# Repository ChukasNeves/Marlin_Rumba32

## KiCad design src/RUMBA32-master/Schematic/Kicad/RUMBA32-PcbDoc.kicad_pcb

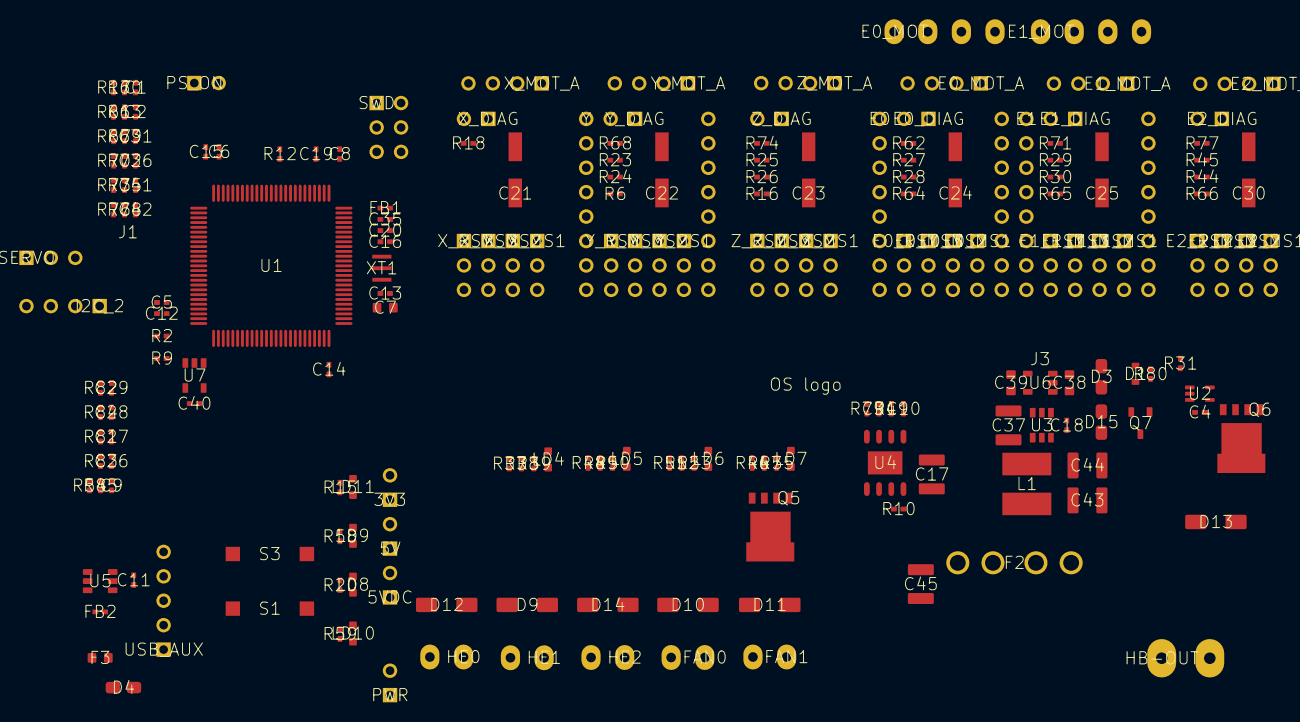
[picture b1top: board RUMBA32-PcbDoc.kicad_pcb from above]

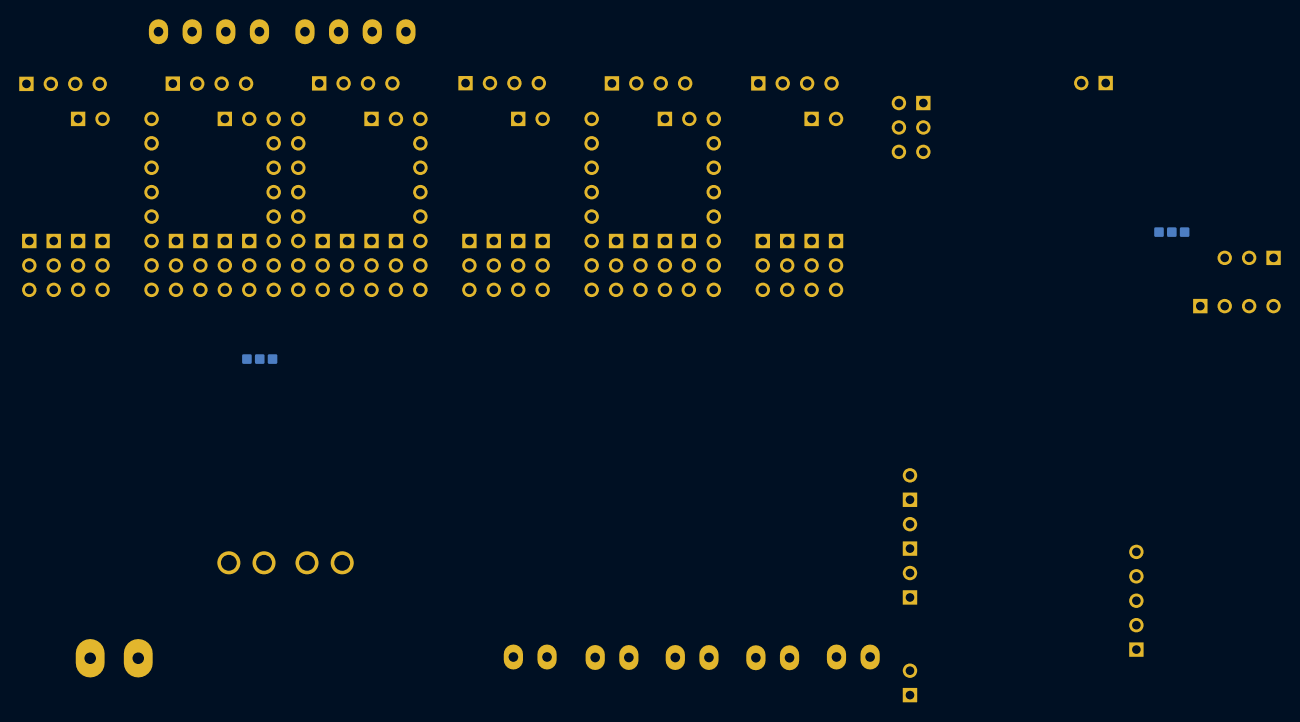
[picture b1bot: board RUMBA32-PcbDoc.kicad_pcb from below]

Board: 4 copper layers, 200 parts (3 on the bottom side), 140 nets, no tracks yet.

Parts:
3V3: 3V3; HDR1X2-HEADER
5V: 5V; HDR1X2-HEADER
5VDC: 5VDC; HDR1X2-HEADER
C1: C1; CAPC1005X55N
C2: C2; CAPC1005X55N
C4: C4; CAP 1005-0402
C5: C5; CAP 1005-0402
C6: C6; CAP 1005-0402
C7: C7; CAPC1608X90N
C8: C8; CAP 1005-0402
C9: C9; CAPC1005X55N
C10: C10; CAP 1005-0402
C11: C11; CAP 1005-0402
C12: C12; CAPC1005X55N
C13: C13; CAP 1005-0402
C14: C14; CAP 1005-0402
C15: C15; CAP 1005-0402
C16: C16; CAP 1005-0402
C17: C17; CAPC3225X220N
C18: C18; CAP 1005-0402
C19: C19; CAP 1005-0402
C20: C20; CAP 1005-0402
C21: C21; CAP EL PANASONIC
C22: C22; CAP EL PANASONIC
C23: C23; CAP EL PANASONIC
C24: C24; CAP EL PANASONIC
C25: C25; CAP EL PANASONIC
C26: C26; CAPC1005X55N
C27: C27; CAPC1005X55N
C28: C28; CAPC1005X55N
C29: C29; CAPC1005X55N
C30: C30; CAP EL PANASONIC
C31: C31; CAPC1005X55N
C34: C34; CAP 1005-0402
C35: C35; CAP 1005-0402
C36: C36; CAPC1005X55N
C37: C37; CAPC3225X220N
C38: C38; CAPC1608X90N
C39: C39; CAPC1608X90N
C40: C40; CAP 1005-0402
C41: C41; CAPC1005X55N
C42: C42; CAPC1005X55N
C43: C43; CAPC3225X220N
C44: C44; CAPC3225X220N
C45: C45; CAPC3225X220N
D1: D1; SOD523
D3: D3; DIOM2616X08N
D4: D4; DIOM2616X08N
D9: D9; DO-214AC
D10: D10; DO-214AC
D11: D11; DO-214AC
D12: D12; DO-214AC
D13: D13; DO-214AC
D14: D14; DO-214AC
D15: D15; DIOM2616X08N
E0: E0; A4988BREAKOUT_2
E0_DIAG: E0_DIAG; HDR1X2-HEADER Female
E0_MOT: E0_MOT; TERM4 3.5MM
E0_MOT_A: E0_MOT_A; HDR1X4
E0_MS1: E0_MS1; HDR1X3-HEADER
E0_MS2: E0_MS2; HDR1X3-HEADER
E0_MS3: E0_MS3; HDR1X3-HEADER
E0_RST: E0_RST; HDR1X3-HEADER
E1: E1; A4988BREAKOUT_2
E1_DIAG: E1_DIAG; HDR1X2-HEADER Female
E1_MOT: E1_MOT; TERM4 3.5MM
E1_MOT_A: E1_MOT_A; HDR1X4
E1_MS1: E1_MS1; HDR1X3-HEADER
E1_MS2: E1_MS2; HDR1X3-HEADER
E1_MS3: E1_MS3; HDR1X3-HEADER
E1_RST: E1_RST; HDR1X3-HEADER
E2_DIAG: E2_DIAG; HDR1X2-HEADER Female
E2_MOT_A: E2_MOT_A; HDR1X4
E2_MS1: E2_MS1; HDR1X3-HEADER
E2_MS2: E2_MS2; HDR1X3-HEADER
E2_MS3: E2_MS3; HDR1X3-HEADER
E2_RST: E2_RST; HDR1X3-HEADER
F2: F2; FUSEHOLDER - BK-6013 - MINI ATC ATO BLADE 15A
F3: F3; FUSE 1608-0603
FAN0: FAN0; TERM2 3.5MM
FAN1: FAN1; TERM2 3.5MM
FB1: FB1; RESC1005X40N
FB2: FB2; RESC1005X40N
HB-OUT: HB-OUT; TERM2 5MM
HE0: HE0; TERM2 3.5MM
HE1: HE1; TERM2 3.5MM
HE2: HE2; TERM2 3.5MM
I2C_2: I2C_2; HDR1X4-HEADER
J1: J1; Jump_3Way - SMALL
J3: J3; Jump_3Way - SMALL
L1: L1; SRN6045TA SMD Inductor
LD4: LD4; LED 1608-0603
LD5: LD5; LED 1608-0603
LD6: LD6; LED 1608-0603
LD7: LD7; LED 1608-0603
LD8: LD8; LED 1608-0603
LD9: LD9; LED 1608-0603
LD10: LD10; LED 1608-0603
LD11: LD11; LED 1608-0603
OS logo: OS logo; OS LOGO TOP
PS_ON: PS_ON; HDR1X2-HEADER
PWR: PWR; HDR1X2-HEADER
Q5: Q5; LFPACK
Q6: Q6; LFPACK
Q7: Q7; SOT23-3 New
R2: R2; RESC1005X40N
R6: R6; RESC1005X40N
R9: R9; RESC1005X40N
R10: R10; RESC1005X40N
R12: R12; RESC1005X40N
R15: R15; RESC1005X40N
R16: R16; RESC1005X40N
R17: R17; RESC1005X40N
R18: R18; RESC1005X40N
R19: R19; RESC1005X40N
R20: R20; RESC1005X40N
R23: R23; RESC1005X40N
R24: R24; RESC1005X40N
R25: R25; RESC1005X40N
R26: R26; RESC1005X40N
R27: R27; RESC1005X40N
R28: R28; RESC1005X40N
R29: R29; RESC1005X40N
R30: R30; RESC1005X40N
R31: R31; RESC1005X40N
R37: R37; RESC1005X40N
R38: R38; RESC1005X40N
R39: R39; RESC1005X40N
R44: R44; RESC1005X40N
R45: R45; RESC1005X40N
R46: R46; RESC1005X40N
R47: R47; RESC1005X40N
R48: R48; RESC1005X40N
R49: R49; RESC1005X40N
R50: R50; RESC1005X40N
R51: R51; RESC1005X40N
R52: R52; RESC1005X40N
R53: R53; RESC1005X40N
R54: R54; RESC1005X40N
R55: R55; RESC1005X40N
R58: R58; RESC1005X40N
R59: R59; RESC1005X40N
R60: R60; RESC1005X40N
R61: R61; RESC1005X40N
R62: R62; RESC1005X40N
R63: R63; RESC1005X40N
R64: R64; RESC1005X40N
R65: R65; RESC1005X40N
R66: R66; RESC1005X40N
R67: R67; RESC1005X40N
R68: R68; RESC1005X40N
R69: R69; RESC1005X40N
R70: R70; RESC1005X40N
R71: R71; RESC1005X40N
R72: R72; RESC1005X40N
R73: R73; RESC1005X40N
R74: R74; RESC1005X40N
R75: R75; RESC1005X40N
R76: R76; RESC1005X40N
R77: R77; RESC1005X40N
R78: R78; RESC1005X40N
R79: R79; RESC1005X40N
R80: R80; RESC1005X40N
R81: R81; RESC1005X40N
R82: R82; RESC1005X40N
R83: R83; RESC1005X40N
R84: R84; RESC1005X40N
R85: R85; RESC1005X40N
S1: S1; SW-PB SMD 2pin
S3: S3; SW-PB SMD 2pin
SERVO: SERVO; HDR1X3-HEADER
SWD: SWD; HDR2X3
U1: U1; STM-LQFP100_N
U2: U2; SOT353
U3: U3; TSOT23-6
U4: U4; SOIC127P600X170_HS-9N
U5: U5; TSOT23-6
U6: U6; SOT23-5
U7: U7; SOT23-5
USB_AUX: USB_AUX; HDR1X5-HEADER
XT1: XT1; CERALOCK CSTCE_G
X_DIAG: X_DIAG; HDR1X2-HEADER Female
X_MOT_A: X_MOT_A; HDR1X4
X_MS1: X_MS1; HDR1X3-HEADER
X_MS2: X_MS2; HDR1X3-HEADER
X_MS3: X_MS3; HDR1X3-HEADER
X_RST: X_RST; HDR1X3-HEADER
Y: Y; A4988BREAKOUT_2
Y_DIAG: Y_DIAG; HDR1X2-HEADER Female
Y_MOT_A: Y_MOT_A; HDR1X4
Y_MS1: Y_MS1; HDR1X3-HEADER
Y_MS2: Y_MS2; HDR1X3-HEADER
Y_MS3: Y_MS3; HDR1X3-HEADER
Y_RST: Y_RST; HDR1X3-HEADER
Z_DIAG: Z_DIAG; HDR1X2-HEADER Female
Z_MOT_A: Z_MOT_A; HDR1X4
Z_MS1: Z_MS1; HDR1X3-HEADER
Z_MS2: Z_MS2; HDR1X3-HEADER
Z_MS3: Z_MS3; HDR1X3-HEADER
Z_RST: Z_RST; HDR1X3-HEADER

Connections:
5V_DCDC: 5VDC.1, C43.2, C44.2, D15.A, L1.2, LD8.1, R79.2, U3.1
+3V3: 3V3.1, C7.2, C12.2, C13.2, C14.2, C15.2, C16.2, C19.2, C39.2, C40.2, FB1.2, J1.1, J3.1, LD11.1, R2.2, S3.1, SWD.2, U1.6, U1.11, U1.19, U1.28, U1.50, U1.75, U1.100, U6.5, U7.4
+3V3A: C20.2, C35.2, FB1.1, R54.1, U1.21, U1.22
+5V: 5V.1, C4.2, C38.2, D3.A, D4.K, D15.K, I2C_2.4, J1.3, J3.3, LD9.1, R80.2, SERVO.2, U2.5, U6.1, U6.3
+12V: C45.2, LD10.1
+DRV: E0.10, E0_MS1.1, E0_MS2.1, E0_MS3.1, E1.10, E1_MS1.1, E1_MS2.1, E1_MS3.1, E2_MS1.1, E2_MS2.1, E2_MS3.1, J3.2, R23.1, R25.1, R27.1, R29.1, R45.1, X_MS1.1, X_MS2.1, X_MS3.1, Y.10, Y_MS1.1, Y_MS2.1, Y_MS3.1, Z_MS1.1, Z_MS2.1, Z_MS3.1
+V_STOP: J1.2, R17.1, R61.1, R67.1, R70.1, R73.1, R76.1
BOOT0: S3.2, SWD.4, U1.94
BTN_EN2: R12.2, U1.37
E0-CS/RX: E0_MS3.3, R64.1, U1.7
E0-DIR: E0.8, U1.92
E0-EN: E0.1, R27.2, U1.80
E0-SLP: E0.6, E0_RST.1
E0-STEP: E0.7, U1.91
E0-TX: R64.2, U1.58
E1-CS/RX: E1_MS3.3, R65.1, U1.86
E1-DIR: E1.8, U1.88
E1-EN: E1.1, R29.2, U1.85
E1-SLP: E1.6, E1_RST.1
E1-STEP: E1.7, U1.87
E1-TX: R65.2, U1.89
E2-CS/RX: E2_MS3.3, R66.1, U1.82
E2-EN: R45.2, U1.81
E2-TX: R66.2, U1.90
FAN_0: R46.1, R47.1, R55.2, U1.67
FAN_1: R51.1, R52.1, R53.2, U1.66
GND: 3V3.2, 5V.2, 5VDC.2, C1.1, C2.1, C4.1, C5.1, C6.1, C7.1, C8.1, C9.1, C10.2, C11.1, C12.1, C13.1, C14.1, C15.1, C16.1, C17.1, C19.1, C20.1, C21.2, C22.2, C23.2, C24.2, C25.2, C26.1, C27.1, C28.1, C29.1, C30.2, C31.1, C34.1, C35.1, C36.1, C37.1, C38.1, C39.1, C40.1, C41.1, C42.1, C43.1, C44.1, C45.1, E0.9, E0.15, E1.9, E1.15, FB2.2, I2C_2.3, LD4.2, LD5.2, LD6.2, LD7.2, PS_ON.2, PWR.2, Q5.3, Q6.3, R10.1, R12.1, R15.1, R20.1, R24.2, R26.2, R28.2, R30.2, R38.2, R44.2, R47.2, R49.2, R52.2, R58.1, R59.1, S1.2, SERVO.1, SWD.6, U1.10, U1.20, U1.27, U1.49, U1.74, U1.99, U2.3, U3.4, U4.3, U5.2, U6.2, U7.2, U7.5, USB_AUX.2, XT1.2, Y.9, Y.15
HB: R31.1, U1.24
HE_1: R37.1, R38.1, R39.2, U1.64
HE_2: R48.1, R49.1, R50.2, U1.65
NetC5_2: C5.2, U1.73
NetC6_2: C6.2, U1.48
NetC10_1: C10.1, R19.1
NetC18_1: C18.1, L1.1, U3.5
NetC18_2: C18.2, U3.6
NetC34_2: C34.2, U4.7
NetD1_A: D1.A, Q7.1, R80.1
NetD4_A: D4.A, F3.2
NetD9_A: D9.A, HE1.2
NetD10_A: D10.A, FAN0.2
NetD10_K: D10.K, FAN0.1
NetD11_A: D11.A, FAN1.2, Q5.2
NetD11_K: D11.K, FAN1.1
NetD12_A: D12.A, HE0.2
NetD13_A: D13.A, HB-OUT.1, Q6.2
NetD14_A: D14.A, HE2.2
NetD14_K: D14.K, HE2.1
NetE0_2: E0.2, E0_MS1.2, R28.1
NetE0_3: E0.3, E0_MS2.2
NetE0_4: E0.4, E0_MS3.2
NetE0_5: E0.5, E0_RST.2
NetE0_11: E0.11, E0_MOT.1, E0_MOT_A.4
NetE0_12: E0.12, E0_MOT.2, E0_MOT_A.3
NetE0_13: E0.13, E0_MOT.3, E0_MOT_A.2
NetE0_14: E0.14, E0_MOT.4, E0_MOT_A.1
NetE0_DIAG_1: E0_DIAG.1, R62.1
NetE1_2: E1.2, E1_MS1.2, R30.1
NetE1_3: E1.3, E1_MS2.2
NetE1_4: E1.4, E1_MS3.2
NetE1_5: E1.5, E1_RST.2
NetE1_11: E1.11, E1_MOT.1, E1_MOT_A.4
NetE1_12: E1.12, E1_MOT.2, E1_MOT_A.3
NetE1_13: E1.13, E1_MOT.3, E1_MOT_A.2
NetE1_14: E1.14, E1_MOT.4, E1_MOT_A.1
NetE1_DIAG_1: E1_DIAG.1, R71.1
NetE2_2: E2_MS1.2, R44.1
NetE2_DIAG_1: E2_DIAG.1, R77.1
NetFB2_1: FB2.1, USB_AUX.1
NetLD4_1: LD4.1, R39.1
NetLD5_1: LD5.1, R50.1
NetLD6_1: LD6.1, R53.1
NetLD7_1: LD7.1, R55.1
NetLD8_2: LD8.2, R20.2
NetLD9_2: LD9.2, R58.2
NetLD10_2: LD10.2, R59.2
NetLD11_2: LD11.2, R15.2
NetQ5_1: Q5.1, R46.2
NetQ6_1: Q6.1, U2.4
NetR9_1: R9.1, U1.96
NetR10_2: R10.2, U4.4
NetR17_2: R17.2, R60.1
NetR18_1: R18.1, X_DIAG.1
NetR19_2: R19.2, U4.5
NetR24_1: R24.1, Y.2, Y_MS1.2
NetR26_1: R26.1, Z_MS1.2
NetR31_2: R31.2, U2.2
NetR61_2: R61.2, R63.1
NetR67_2: R67.2, R69.1
NetR68_1: R68.1, Y_DIAG.1
NetR70_2: R70.2, R72.1
NetR73_2: R73.2, R75.1
NetR74_1: R74.1, Z_DIAG.1
NetR76_2: R76.2, R78.1
NetR79_1: R79.1, U4.8
NetU1_12: U1.12, XT1.3
NetU1_13: U1.13, XT1.1
NetY_3: Y.3, Y_MS2.2
NetY_4: Y.4, Y_MS3.2
NetY_5: Y.5, Y_RST.2
NetY_11: Y.11, Y_MOT_A.4
NetY_12: Y.12, Y_MOT_A.3
NetY_13: Y.13, Y_MOT_A.2
NetY_14: Y.14, Y_MOT_A.1
PS_ON: PS_ON.1, U1.42
RESET: C8.2, S1.1, SWD.5, U1.14
SCL: I2C_2.1, R2.1, U7.1
SDA: I2C_2.2, R9.2, U7.3
SERVO: SERVO.3, U1.77
SPI1_MISO: E0_RST.3, E1_RST.3, E2_RST.3, U1.31, X_RST.3, Y_RST.3, Z_RST.3
SPI1_MOSI: E0_MS1.3, E1_MS1.3, E2_MS1.3, U1.32, X_MS1.3, Y_MS1.3, Z_MS1.3
SPI1_SCK: E0_MS2.3, E1_MS2.3, E2_MS2.3, U1.30, X_MS2.3, Y_MS2.3, Z_MS2.3
SWCLK: SWD.3, U1.76
SWDIO: R6.2, SWD.1, U1.72
THERM0_ADC: C29.2, R82.2, U1.33
THERM1_ADC: C28.2, R84.2, U1.18
THERM2_ADC: C27.2, R81.2, U1.17
THERM3_ADC: C26.2, R83.2, U1.16
THERM4: R54.2, R85.1
THERM4_ADC: C9.2, R85.2, U1.15
USBVCC: C11.2, F3.1, U5.5, USB_AUX.5
USB_N: U5.1, USB_AUX.4
USB_P: U5.3, USB_AUX.3
VIN1: C17.2, C37.2, D9.K, D12.K, F2.0, HE0.1, HE1.1, PWR.1, Q7.3, U3.2, U3.3, U4.9
VIN2: D13.K, HB-OUT.2
VMOT: C21.1, C22.1, C23.1, C24.1, C25.1, C30.1, D1.K, D3.K, E0.16, E1.16, Q7.2, Y.16
X-CS/RX: U1.8, X_MS3.3
X-MAX: C2.2, R62.2, R63.2, U1.52
X-MIN: C1.2, R18.2, R60.2, U1.51
Y-CS/RX: R6.1, U1.3, Y_MS3.3
Y-DIR: U1.5, Y.8
Y-EN: R23.2, U1.2, Y.1
Y-MAX: C36.2, R71.2, R72.2, U1.55
Y-MIN: C31.2, R68.2, R69.2, U1.54
Y-SLP: Y.6, Y_RST.1
Y-STEP: U1.4, Y.7
Z-CS/RX: R16.1, U1.97, Z_MS3.3
Z-EN: R25.2, U1.93
Z-MAX: C42.2, R77.2, R78.2, U1.57
Z-MIN: C41.2, R74.2, R75.2, U1.56
Z-TX: R16.2, U1.47

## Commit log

2021-11-03 added gitignore
2021-11-03 merged from bugfix 2xx added configuration for Anycubic Replicator using the Rumba32 board
2022-03-22 chnaged serial port to -1
